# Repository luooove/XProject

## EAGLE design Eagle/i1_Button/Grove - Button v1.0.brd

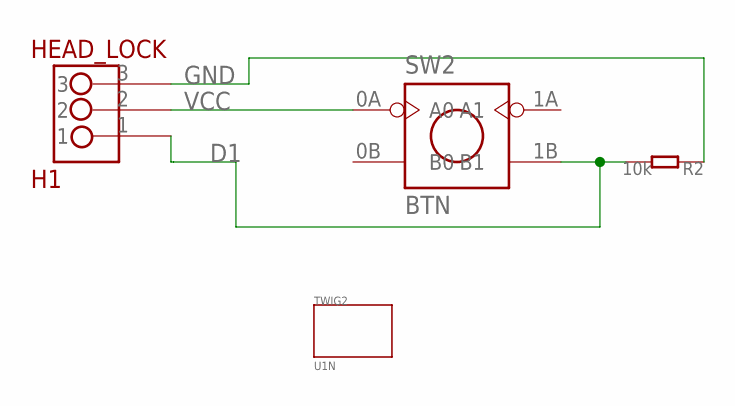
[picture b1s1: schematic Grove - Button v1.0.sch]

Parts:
H1: HEAD_LOCK
R2: 10k; 0603
SW2: BTN; BTN_8X8
TWIG2: U1N

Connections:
D1: H1.1, R2.2, SW2.1B (B1)
GND: H1.3, R2.1
VCC: H1.2, SW2.0A (A0)

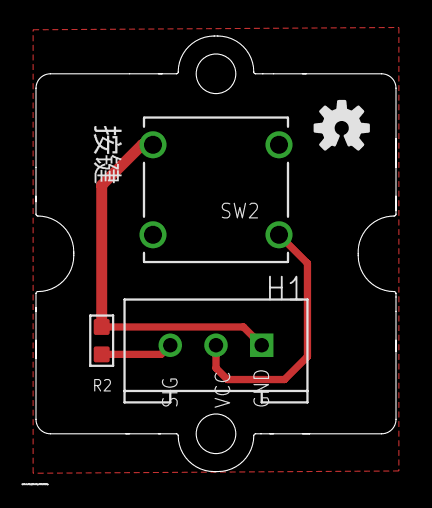
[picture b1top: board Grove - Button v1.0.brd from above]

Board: 2 copper layers, 20.0 x 24.2 mm, 5 parts (0 on the bottom side), 3 nets.

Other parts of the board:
U$2: OSHW-LOGO-S

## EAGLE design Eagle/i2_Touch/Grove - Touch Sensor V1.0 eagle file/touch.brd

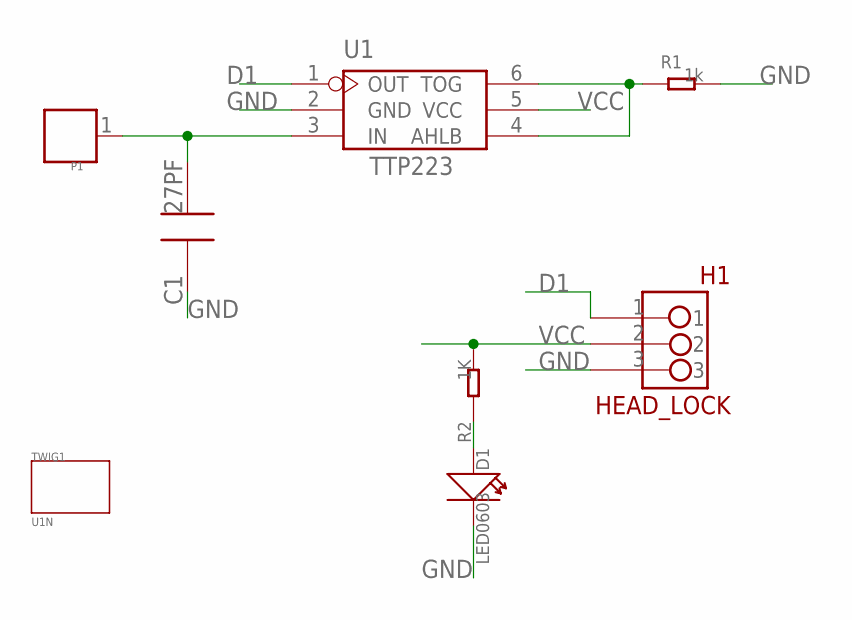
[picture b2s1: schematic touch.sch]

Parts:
C1: 27PF; 0603
D1: LED0603
H1: HEAD_LOCK
P1: PAD'D450MIL'; 1P-D450
R1: 1k; 0603
R2: 1K; 0603
TWIG1: U1N
U1: TTP223; SOT23-6L

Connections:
D1: H1.1, U1.1 (OUT)
GND: C1.1, D1.2 (-), H1.3, R1.2, U1.2 (GND)
IN: C1.2, P1.1, U1.3 (IN)
unnamed: R1.1, U1.4 (AHLB), U1.6 (TOG)
unnamed: D1.1 (+), R2.1
VCC: H1.2, R2.2, U1.5 (VCC)

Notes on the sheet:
TTP223

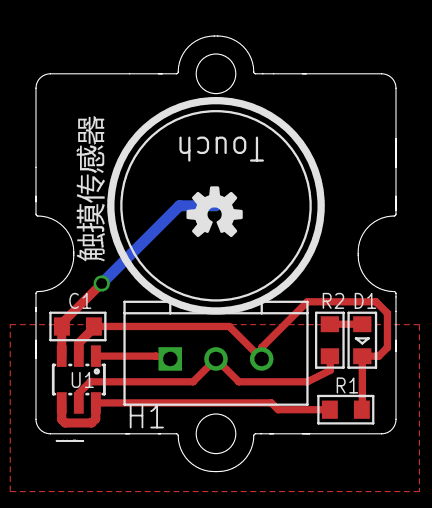
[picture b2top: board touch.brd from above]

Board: 2 copper layers, 20.0 x 24.2 mm, 9 parts (1 on the bottom side), 6 nets.

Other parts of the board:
U$2: OSHW-LOGO-S

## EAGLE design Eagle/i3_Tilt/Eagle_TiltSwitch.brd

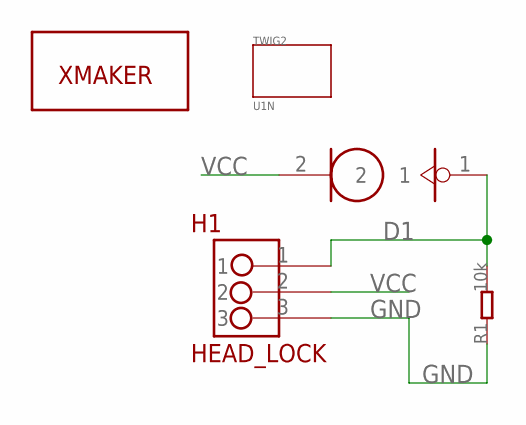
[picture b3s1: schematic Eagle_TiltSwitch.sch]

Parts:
H1: HEAD_LOCK
J1: TILT
R1: 10k; 0603
TWIG2: U1N
U$2: XMAKERLOGO

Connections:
D1: H1.1, J1.1, R1.2
GND: H1.3, R1.1
VCC: H1.2, J1.2

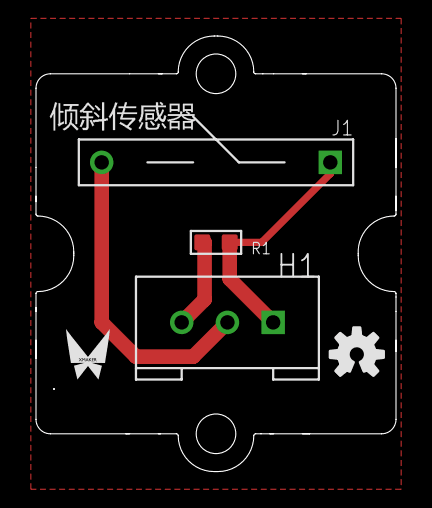
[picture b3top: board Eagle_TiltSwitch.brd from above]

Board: 2 copper layers, 20.0 x 24.2 mm, 6 parts (0 on the bottom side), 3 nets.

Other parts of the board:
U$1: OSHW-LOGO-S

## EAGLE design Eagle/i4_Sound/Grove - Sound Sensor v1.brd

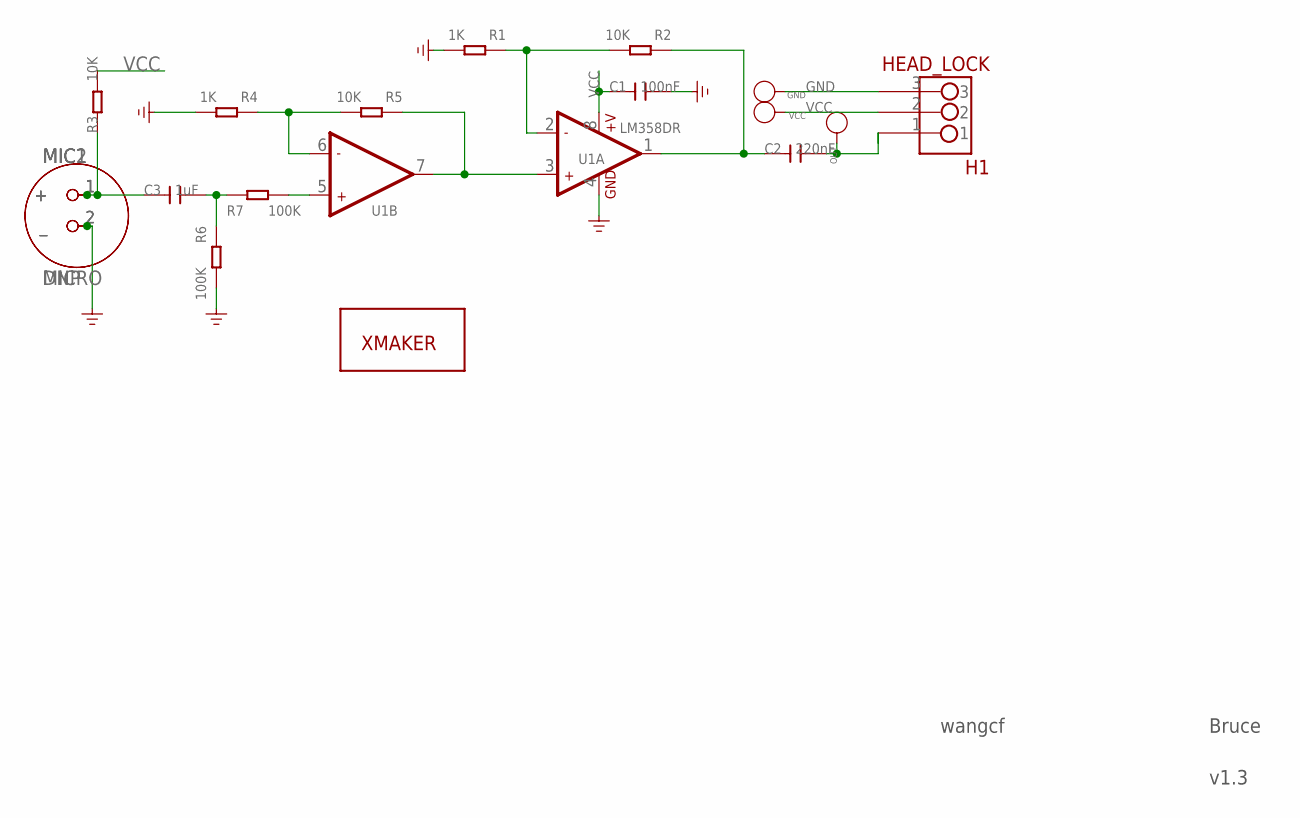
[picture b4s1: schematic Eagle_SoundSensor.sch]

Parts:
C1: 100nF; C0603
C2: 220nF; C0603
C3: 1uF; C0603
GND: PAD-TEST-POINT'4545'; TP_4545
H1: HEAD_LOCK
MIC1: MICRO
MIC2: DNP; MICRO
OUT: PAD-TEST-POINT'4545'; TP_4545
R1, R4: 1K; R0603
R2, R3, R5: 10K; R0603
R6, R7: 100K; R0603
U1: LM358DR; SO08
U$7: XMAKERLOGO
VCC: PAD-TEST-POINT'4545'; TP_4545

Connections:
GND: C1.2, GND.T, H1.3, MIC1.2 (_), MIC2.2 (_), R1.2, R4.2, R6.2, U1.4 (GND)
unnamed: R7.2, U1.5 (+IN2)
unnamed: R4.1, R5.2, U1.6 (-IN2)
unnamed: C3.2, R6.1, R7.1
unnamed: C3.1, MIC1.1 (+), MIC2.1 (+), R3.1
unnamed: R5.1, U1.3 (+IN1), U1.7 (OUT2)
unnamed: R1.1, R2.2, U1.2 (-IN1)
OUT: C2.2, H1.1, OUT.T
OUT1: C2.1, R2.1, U1.1 (OUT1)
VCC: C1.1, H1.2, R3.2, U1.8 (+V), VCC.T

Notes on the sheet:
wangcf
Bruce
v1.3

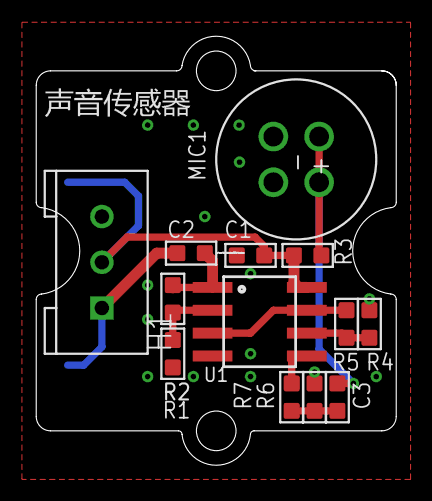
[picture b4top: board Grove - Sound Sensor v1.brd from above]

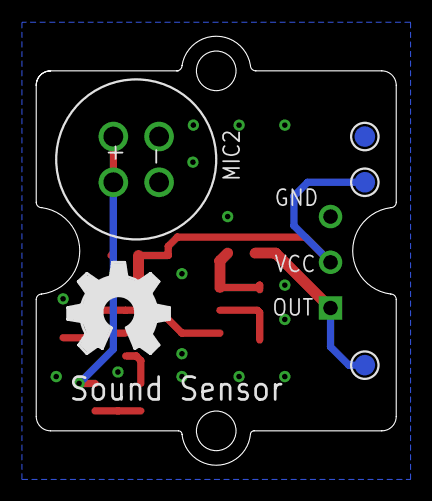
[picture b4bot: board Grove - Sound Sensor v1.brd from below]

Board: 2 copper layers, 20.0 x 23.8 mm, 19 parts (5 on the bottom side), 10 nets.

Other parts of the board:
U$1: OSHW_FILLX200_NOTEXT
U$4: 1U-DIM-W/-DRILL

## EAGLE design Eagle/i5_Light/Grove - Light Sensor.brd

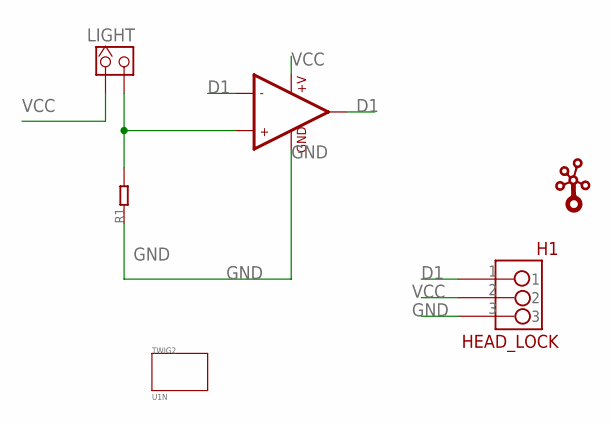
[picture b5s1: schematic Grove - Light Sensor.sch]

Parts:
H1: HEAD_LOCK
LIGHT: HEADER_1X2_2.54; CK_1*2
R1: R0603; 0603
TWIG2: U1N
U1: LMV358; SO08
U$1: TWIGLOGOTWIGLOGO_SMALL; TWIGLOGO_SMALL

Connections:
D1: U1.1 (OUT1), U1.2 (-IN1)
GND: H1.3, R1.1, U1.4 (GND)
unnamed: LIGHT.2, R1.2, U1.3 (+IN1)
VCC: H1.2, LIGHT.1, U1.8 (+V)

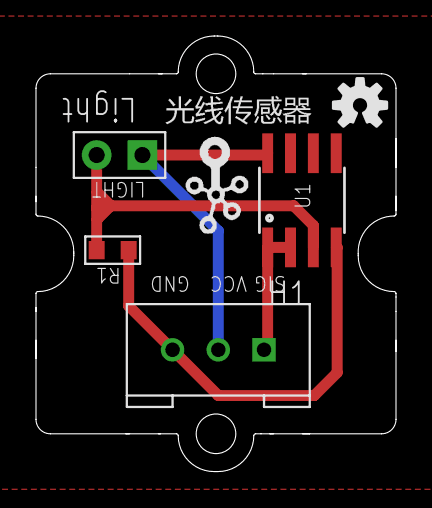
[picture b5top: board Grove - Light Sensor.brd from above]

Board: 2 copper layers, 20.0 x 24.2 mm, 7 parts (0 on the bottom side), 4 nets.

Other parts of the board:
U$3: OSHW-LOGO-S

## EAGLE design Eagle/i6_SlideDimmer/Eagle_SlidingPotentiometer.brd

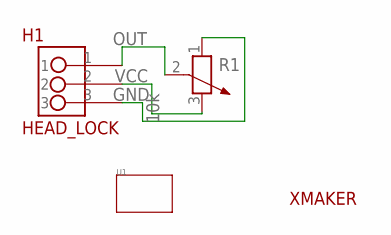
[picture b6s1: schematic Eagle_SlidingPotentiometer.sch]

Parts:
H1: HEAD_LOCK
R1: 10k; 3P-SQUA-45.6X10X5.8H
U1: TWIG'3U'; 3U-DIM-W/-DRILL
U$1: XMAKERLOGO2

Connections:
GND: H1.3, R1.1
OUT: H1.1, R1.2 (3)
VCC: H1.2, R1.3 (2)

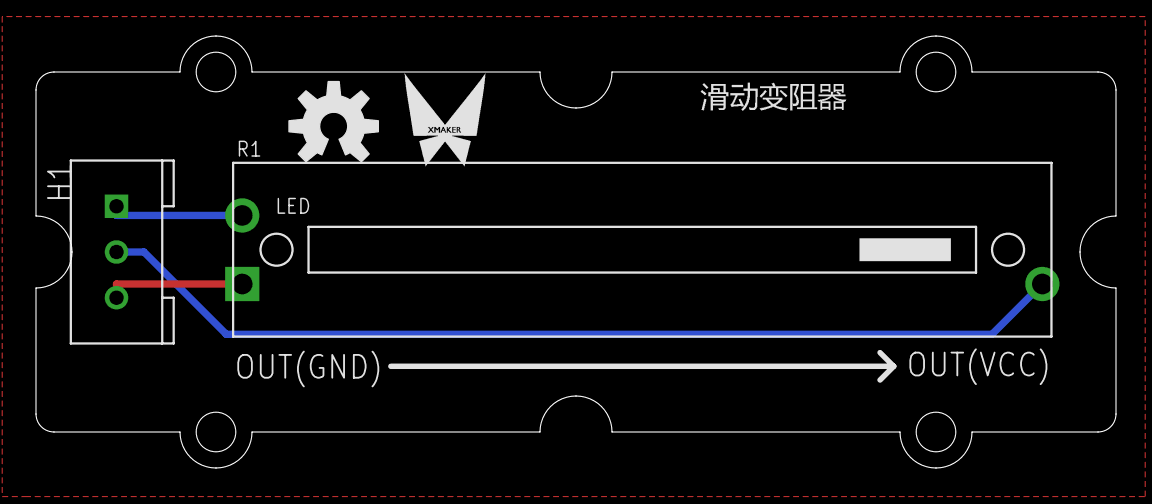
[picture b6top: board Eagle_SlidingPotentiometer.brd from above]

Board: 2 copper layers, 60.0 x 24.0 mm, 5 parts (0 on the bottom side), 3 nets.

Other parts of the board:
U$3: OPENHARDWARE

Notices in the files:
parts and their libraries:
SparkFun-Aesthetics: Licensing: Creative Commons ShareAlike 4.0 International - https://creativecommons.org/licenses/by-sa/4.0
